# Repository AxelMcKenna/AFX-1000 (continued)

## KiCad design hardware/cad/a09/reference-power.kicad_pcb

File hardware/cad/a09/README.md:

# A09 housing with the actual standalone power PCB

Open `assembly.scad` in OpenSCAD. A09 retains A08's RMX-style panel, 29 guided buttons, ten shaft-mount knobs, selectors, optics and release lever. It integrates the actual 84 × 38 × 1.6 mm in-progress higher-headroom supply PCB instead of the old 78 mm generic reserve. This variant remains separate from the B1 budget design.

The supply board moves from X=207 to X=201 mm, at Y=105 and Z=6.5 mm. Its four mount centres are (205,109), (275,109), (205,139) and (275,139). The right edge remains X=285. At the original position, the allocated test-header top was only 0.09 mm below the Scene Resonance pot body. The new position clears that control without reducing its component reserve. The four power mounts now have Ø2.2 through bores for M2 fixings; actual fastener length, bottom retention and feet remain to be selected.

`integration.py` reads both-side courtyards, through-hole lead positions, four mounting holes and the board outline directly from the current KiCad PCB. All 157 components appear individually. The old generic power-component block is removed. Header/harness, trimmed lead/solder, fixing-head and underside thermal-air allowances are explicit. All body heights are **maximum assembly allocations requiring part selection or measurement**, not catalogue guarantees. The smallest allocated floor clearance is 0.35 mm beneath a bottom 1210 capacitor.

Native checks retain the full button stroke and 0–35° lever sweep. Additional checks expand all power component/lead/head reserves by 0.25 mm against the housing, controls, other boards and electronics reserves, and check one millimetre of unobstructed air under the existing thermal-copper regions. These establish geometric clearance for these allocations only; they do not establish cooling, electrical readiness or physical fit.

A09 is isolated under `build/workspaces/high-headroom-standalone`; the active main working tree's A08 files are untouched. `source.json` records the inherited A08 source hashes. `reference-components.scad` freezes the other A08 electronics reserves. Future PCB placement or height changes require regeneration and renewed native checks.

## Rebuild

From the repository root, use the [uv environment](../../../README.md#python-tooling) and a native OpenSCAD build with Manifold and CGAL:

```sh
uv run --locked python hardware/cad/a09/build.py --openscad /path/to/openscad
uv run --locked python -m unittest discover -s tests -p a09_integration_tests.py -v
uv run --locked python -m hardware.cad.a09.verify
```

Outputs go to `build/artifacts/cad/a09/`. The 3MF is a quantity-correct inventory, not a printer profile. Use `parts.csv` and [PRINTING.md](PRINTING.md) for the prototype mechanical inventory. No print-pack path from A07 or A08 is overwritten. The supplied PCB is an in-progress placement/routing source, not a fabrication file.

Additional standalone circuit boards still need routing and housing integration; the frozen A08 reserves do not represent all higher-headroom circuits. Physical printing, selected-part dimensions, wiring and cable bends, board fastening/feet, control feel, optics, thermal/EMI tests and completion of the electrical system remain open. No complete-unit build readiness is claimed.

A09 now retains its checked 84 × 38 mm supply snapshot in `reference-power.kicad_pcb` and `reference-power-components.json`. The active larger-board integration is [A10](../a10/README.md); rebuilding A09 uses these frozen inputs. The original review archives are unchanged.

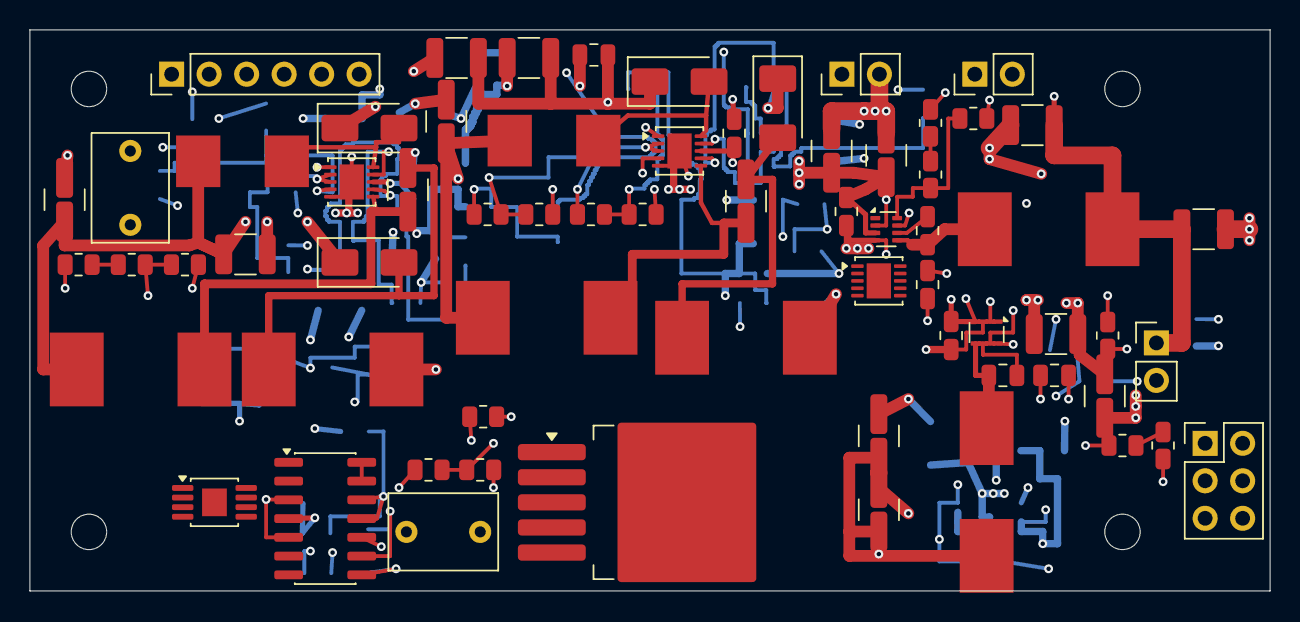
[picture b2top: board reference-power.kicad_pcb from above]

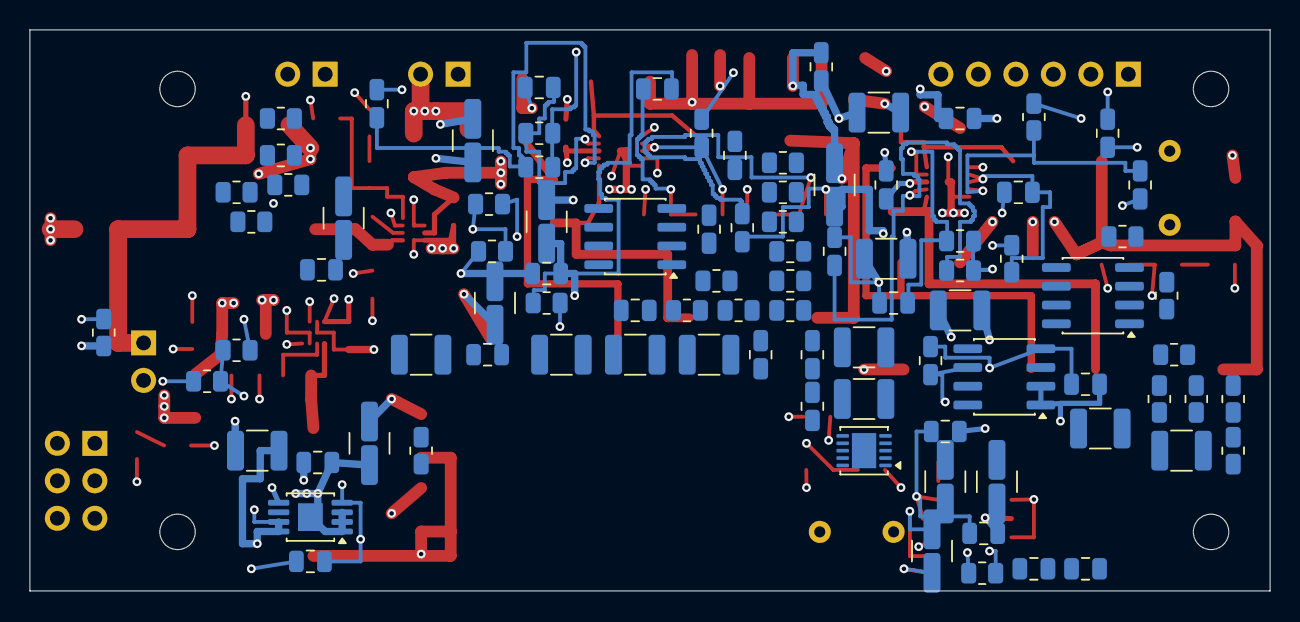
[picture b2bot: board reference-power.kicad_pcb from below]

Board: 6 copper layers, 84.0 x 38.0 mm, 161 parts (91 on the bottom side), 67 nets.

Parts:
C1, C63: 10uF 63V X7R; C_1210_3225Metric
C2, C3, C5, C6, C8, C9, C37, C42, C47, C52, C57, C64, C65, C67, C68, C70: 22uF 50V X7R; C_1210_3225Metric
C4, C7, C10, C22, C29, C35, C38, C40, C43, C45, C48, C50, C53, C55, C58, C59, C61, C66, C69, C71: 100nF 50V X7R; C_0805_2012Metric
C11, C16, C23, C30, C72: 100nF 16V X7R; C_0805_2012Metric
C12, C14, C73, C75: 68pF 50V C0G 5%; C_0805_2012Metric
C13, C15, C74, C76: 330nF 16V X7R; C_0805_2012Metric
C17: 1uF 16V X7R; C_0805_2012Metric
C18, C19, C25, C26: 22uF 16V X7R; C_1210_3225Metric
C20, C21, C27, C28: 10uF 25V X7R; C_1210_3225Metric
C24: 33nF 16V X7R; C_0805_2012Metric
C31: 2.2uF 16V X7R; C_0805_2012Metric
C32, C33: 1uF film 63V 10% MKS2C041001F00KSSD; C_Rect_L7.2mm_W5.0mm_P5.00mm
C34, C39, C44, C49, C54: 47nF 50V C0G 5%; C_1210_3225Metric
C36, C41, C46, C51, C56: 10uF 50V X7R; C_1210_3225Metric
C60, C62: 1uF 50V X7R; C_0805_2012Metric
D1, D2, D3, D4: SS16-E3/61T; D_SMA
H1, H2, H3, H4: M2_CLEARANCE; M2_Clearance
J1, J3, J5: Header2; PinHeader_1x02_P2.54mm_Vertical
J2: Header6; PinHeader_1x06_P2.54mm_Vertical
J4: Header6; PinHeader_2x03_P2.54mm_Vertical
L1, L6: 33uH 20% SRP7050WA-330M; SRP7050WA
L2, L3, L7, L8: 68uH 20% SRP1050WA-680M; SRP1050WA
L4, L5: 10uH 20% SRP1050WA-100M; SRP1050WA
R1: 300k 0.01% 5ppm; R_0805_2012Metric
R2, R3, R4, R45, R46: 15k 0.01% 5ppm; R_0805_2012Metric
R5, R20, R21, R34, R35: 330k 0.01% 5ppm; R_0805_2012Metric
R6, R7, R49, R50: 4.7k 1%; R_0805_2012Metric
R8, R12: 10k 1%; R_0805_2012Metric
R9, R13: 22k 1%; R_0805_2012Metric
R10: 10.5k 0.01% 5ppm; R_0805_2012Metric
R11, R16: 2k 0.01% 5ppm; R_0805_2012Metric
R14: 12.4k 0.01% 5ppm; R_0805_2012Metric
R15: 100 0.01% 5ppm; R_0805_2012Metric
R17, R19: 1k 1%; R_0805_2012Metric
R18: 100k 1%; R_0805_2012Metric
R22, R27, R30, R31, R36, R41: 100k 0.01% 5ppm; R_0805_2012Metric
R23, R28, R32, R37, R42: 6.8k 1%; R_0805_2012Metric
R24, R38: 9.09k 1%; R_0805_2012Metric
R25, R39, R47: 200k 0.01% 5ppm; R_0805_2012Metric
R26, R40: 180k 0.01% 5ppm; R_0805_2012Metric
R29, R43: 5.62k 1%; R_0805_2012Metric
R33: 2.21k 1%; R_0805_2012Metric
R44: 240k 0.01% 5ppm; R_0805_2012Metric
R48: 54.9k 0.01% 5ppm; R_0805_2012Metric
R51: 10 0.01% 5ppm; R_0805_2012Metric
U1, U13: LT3471EDD#PBF; DFN-10-1EP_3x3mm_P0.5mm_EP1.65x2.38mm
U2, U3: TPS62933FDRLR; SOT-583-8
U4: REF5025EIDR; SOIC-8_3.9x4.9mm_P1.27mm
U5: OPA4192ID; SOIC-14_3.9x8.7mm_P1.27mm
U6: OPA2192ID; SOIC-8_3.9x4.9mm_P1.27mm
U7, U9: LT3080IMS8E#PBF; MSOP-8-1EP_3x3mm_P0.65mm_EP1.68x1.88mm
U8: LT3080IQ#PBF; TO-263-5_TabPin3
U10, U11: LT3090IDD#PBF; DFN-10-1EP_3x3mm_P0.5mm_EP1.65x2.38mm
U12: LT1634AIS8-2.5#PBF; SOIC-8_3.9x4.9mm_P1.27mm

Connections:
/5V_DIG_SRC: C18.1, C19.1, C30.1, J3.1, L4.2, R6.1, R7.1, R10.1, R49.1, R50.1, U4.1, U4.2, U10.5, U11.5
/AGND: C2.2, C3.2, C4.2, C5.2, C6.2, C7.2, C8.2, C9.2, C10.2, C11.2, C13.2, C15.2, C17.2, C18.2, C19.2, C20.2, C21.2, C22.2, C24.2, C25.2, C26.2, C27.2, C28.2, C29.2, C30.2, C31.2, C32.2, C33.2, C35.2, C36.2, C37.2, C38.2, C40.2, C41.2, C42.2, C43.2, C45.2, C46.2, C47.2, C48.2, C50.2, C51.2, C52.2, C53.2, C55.2, C56.2, C57.2, C58.2, C59.2, C60.2, C61.2, C62.2, C64.2, C65.2, C66.2, C67.2, C68.2, C69.2, C70.2, C71.2, C72.2, C74.2, C76.2, D2.1, D4.1, J1.2, J2.2, J3.2, J4.2, J5.1, R3.2, R9.2, R11.2, R13.2, R16.2, R22.2, R24.2, R27.2, R29.2, R31.2, R33.2, R36.2, R38.2, R41.2, R43.2, R45.2, U1.5, U1.11, U2.4, U3.4, U4.4, U5.11, U5.12, U6.8, U10.3, U11.3, U12.6, U13.5, U13.11
/CUK_NODE: C1.2, D2.2, L3.1
/DIG_BST: C16.1, U2.6
/DIG_FB: R11.1, R51.2, U2.8
/DIG_FB_TRIM: R10.2, R51.1
/DIG_SS: C17.1, U2.7
/DIG_SW: C16.2, L4.1, U2.5
/LO_CUK_NODE: C63.2, D4.2, L8.1
/LO_N_FB: C75.2, R46.2, R47.1, U13.4
/LO_N_RMID: R47.2, R48.1
/LO_N_SS: C76.1, R50.2, U13.7
/LO_N_SW: C63.1, L7.2, U13.6
/LO_P_FB: C73.2, R44.2, R45.1, U13.1
/LO_P_SS: C74.1, R49.2, U13.9
/LO_P_SW: D3.2, L6.2, U13.10
/LO_REF_1V: C72.1, R46.1, U13.2, U13.3
/N12_DRIVE: C54.1, R42.1, U6.7
/N12_FB: C54.2, R40.2, R41.1, U6.6
/N12_RMID: R39.2, R40.1
/N12_SET: C55.1, R39.1, R42.2, U11.4
/N12_SRC: C57.1, C58.1, J2.5, R43.1, U11.1, U11.2
/N19_DRIVE: C49.1, R37.1, U6.1
/N19_FB: C49.2, R35.2, R36.1, U6.2
/N19_RMID: R34.2, R35.1
/N19_SET: C50.1, R34.1, R37.2, U10.4
/N19_SRC: C52.1, C53.1, J2.3, R38.1, U10.1, U10.2
/NREF_2V5: R18.1, R19.1, U12.4, U12.5
/NREF_FILTER: C33.1, R19.2, U6.3, U6.5
/P12_DRIVE: C39.1, R28.1, U5.7
/P12_FB: C39.2, R26.2, R27.1, U5.6
/P12_RMID: R25.2, R26.1
/P12_SET: C40.1, R25.1, R28.2, U8.2
/P12_SRC: C42.1, C43.1, J2.4, R29.1, U8.3
/P19_DRIVE: C34.1, R23.1, U5.1
/P19_FB: C34.2, R21.2, R22.1, U5.2
/P19_RMID: R20.2, R21.1
/P19_SET: C35.1, R20.1, R23.2, U7.4
/P19_SRC: C37.1, C38.1, J2.1, R24.1, U7.1, U7.2, U7.3, U7.9
/POWER_READY: J5.2, R8.1, R12.1
/PREF_2V5: C31.1, R17.1, U4.6
/PREF_FILTER: C32.1, R17.2, U5.3, U5.5, U5.10
/PRE_BST: C23.1, U3.6
/PRE_FB: R15.2, R16.1, U3.8
/PRE_RMID: R14.2, R15.1
/PRE_SS: C24.1, U3.7
/PRE_SW: C23.2, L5.1, U3.5
/RAW_N17: C56.1, C67.1, C68.1, C69.1, C75.1, J4.5, L8.2, R48.2, U11.8, U11.9, U11.10, U11.11
/RAW_N22: C8.1, C9.1, C10.1, C14.1, C51.1, C61.1, C62.1, J4.3, L3.2, R5.2, R18.2, U6.4, U10.8, U10.9, U10.10, U10.11
/RAW_N_FB: C14.2, R4.2, R5.1, U1.4
/RAW_N_SS: C15.1, R7.2, U1.7
/RAW_N_SW: C1.1, L2.2, U1.6
/RAW_P17: C41.1, C64.1, C65.1, C66.1, C73.1, D3.1, J4.4, R44.1, U8.4, U8.5
/RAW_P22: C5.1, C6.1, C7.1, C12.1, C36.1, C59.1, C60.1, D1.1, J4.1, R1.1, U5.4, U7.5, U7.7, U7.8
/RAW_P_FB: C12.2, R2.2, R3.1, U1.1
/RAW_P_RMID: R1.2, R2.1
/RAW_P_SS: C13.1, R6.2, U1.9
/RAW_P_SW: D1.2, L1.2, U1.10
/SPARE_OUT: U5.13, U5.14
/SUPPLY_ENABLE: R8.2, R9.1, R12.2, R13.1, U2.2, U3.2
/SW_REF_1V: C11.1, R4.1, U1.2, U1.3
/V5_PRE: C25.1, C26.1, C46.1, J4.6, L5.2, R14.1, U9.7, U9.8
/V5_REG_DRIVE: C44.1, R32.1, U5.8
/V5_REG_FB: C44.2, R30.2, R31.1, U5.9
/V5_REG_SET: C45.1, R30.1, R32.2, U9.4
/V5_REG_SRC: C47.1, C48.1, J2.6, R33.1, U9.1, U9.2, U9.3, U9.9
/VIN_PROTECTED: C2.1, C3.1, C4.1, C20.1, C21.1, C22.1, C27.1, C28.1, C29.1, C70.1, C71.1, J1.1, L1.1, L2.1, L6.1, L7.1, U1.8, U2.3, U3.3, U9.5, U13.8

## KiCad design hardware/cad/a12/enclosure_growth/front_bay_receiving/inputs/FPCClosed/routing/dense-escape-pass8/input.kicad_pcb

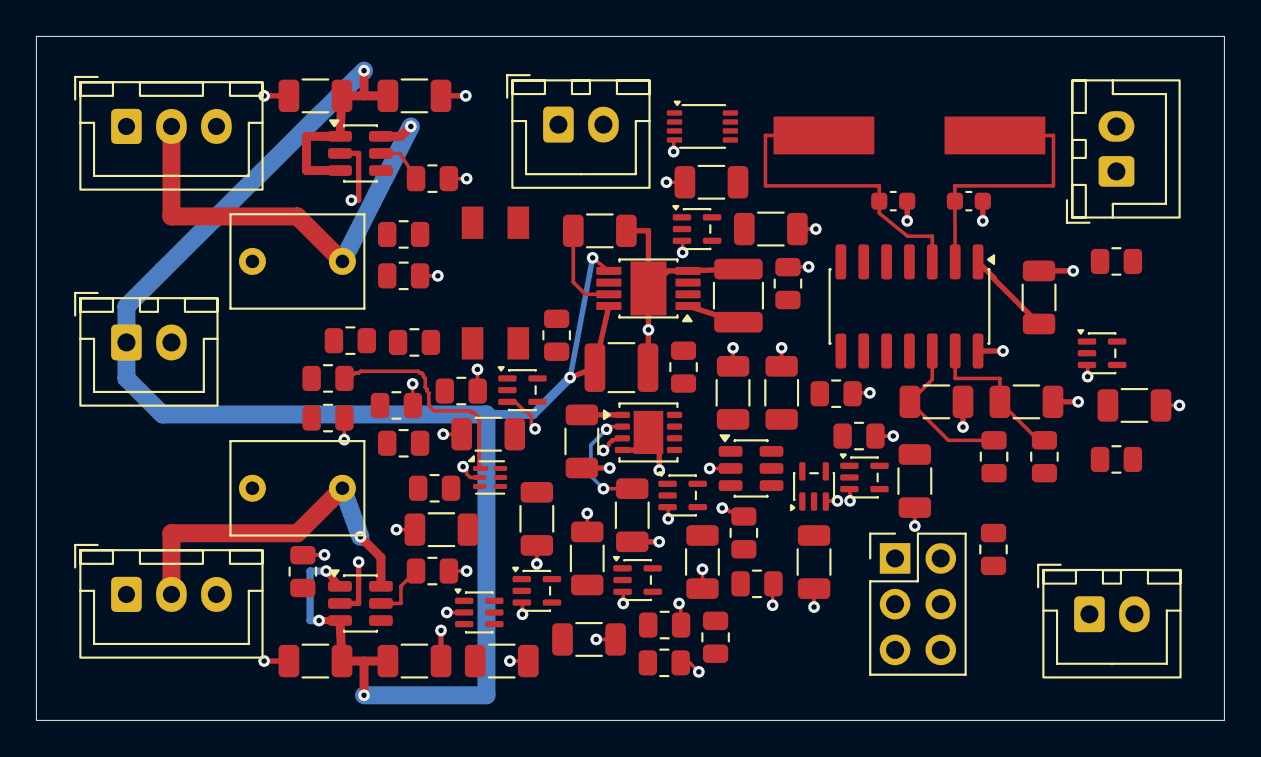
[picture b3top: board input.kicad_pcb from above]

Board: 4 copper layers, 66.0 x 38.0 mm, 84 parts (0 on the bottom side), 45 nets.

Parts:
C1, C2: 10uF 25V C3225X7R1E106K250AC; Capacitor_SMD__C_1210_3225Metric
C3, C14, C22, C23: 10nF 50V C0G C1206C103J5GACTU; Capacitor_SMD__C_1206_3216Metric
C4, C5, C6, C8, C9, C10, C11, C12, C13, C15, C16, C17, C18, C19, C24: 100nF 25V C0G C1206C104J3GACTU; Capacitor_SMD__C_1206_3216Metric
C7: 2.7nF 50V C0G C1206C272J5GACTU; Capacitor_SMD__C_1206_3216Metric
C20, C21: 15pF 50V C0G5% C0603C150J5GACTU; Capacitor_SMD__C_0603_1608Metric
C201, C202, C301, C302: 100nF25V C0G5% C1206C104J3GACTU; Capacitor_SMD__C_1206_3216Metric
C203, C303: 1uF63V10% WIMA MKS2C041001F00KSSD; Capacitor_THT__C_Rect_L7.2mm_W5.0mm_P5.00mm
J2, J3, J4, J201: JST B2B-XH-A / XHP-2 / SXH-001T-P0.6; Connector_JST__JST_XH_B2B-XH-A_1x02_P2.50mm_Vertical
J5: AVRISP2x3 target-powered3.3V sense ONLY; Connector_PinHeader_2.54mm__PinHeader_2x03_P2.54mm_Vertical
J202, J203: JST B3B-XH-A / XHP-3 / SXH-001T-P0.6; Connector_JST__JST_XH_B3B-XH-A_1x03_P2.50mm_Vertical
R1, R16, R17, R21, R23: 1k 0.1%25ppm TNPW08051K00BEEA; Resistor_SMD__R_0805_2012Metric
R2, R6, R10, R13, R202, R302: 10k 0.1%25ppm TNPW080510K0BEEA; Resistor_SMD__R_0805_2012Metric
R3, R4, R5, R7, R14, R15: 47k 0.1%25ppm TNPW080547K0BEEA; Resistor_SMD__R_0805_2012Metric
R8: 68k 0.1%25ppm TNPW080568K0BEEA; Resistor_SMD__R_0805_2012Metric
R9: 39k 0.1%25ppm TNPW080539K0BEEA; Resistor_SMD__R_0805_2012Metric
R11: 56.2k 0.1%25ppm TNPW080556K2BEEA; Resistor_SMD__R_0805_2012Metric
R12, R24, R201, R203, R301, R303: 100k 0.1%25ppm TNPW0805100KBEEA; Resistor_SMD__R_0805_2012Metric
R20, R22: 20k 0.1%25ppm TNPW080520K0BEEA; Resistor_SMD__R_0805_2012Metric
U1: ATtiny84A-SSUR; Package_SO__SOIC-14_3.9x8.7mm_P1.27mm
U2: TPS7A1633DGNR; TI_DGN0008C
U3: SN74LVC2G17DCKR; Package_TO_SOT_SMD__SOT-363_SC-70-6
U4: TPS3431SDRBR; Package_SON__VSON-8-1EP_3x3mm_P0.65mm_EP1.65x2.4mm
U5: SN74AUP1G17DCKR; Package_TO_SOT_SMD__SOT-353_SC-70-5
U6: SN74LVC1T45DBVR; Package_TO_SOT_SMD__SOT-23-6
U7: SN74LVC1G14DCKR; Package_TO_SOT_SMD__SOT-353_SC-70-5
U8: SN74LVC1G74DCUR; TI_DCU0008A
U9: TPS389001DSET; Package_SON__WSON-6_1.5x1.5mm_P0.5mm
U10, U11: SN74LVC1G17DCKR; Package_TO_SOT_SMD__SOT-353_SC-70-5
U12, U13: SN74LVC1G08DCKR; Package_TO_SOT_SMD__SOT-353_SC-70-5
U14: SN74LVC1G06DCKR; Package_TO_SOT_SMD__SOT-353_SC-70-5
U15: TLP175A(TPL,E); RMX_FH02__TLP175A_11-4M1S_Receiving
U16: SN74LVC1G34DCKR; Package_TO_SOT_SMD__SOT-353_SC-70-5
U201, U301: TPS2553DBVR-1; Package_TO_SOT_SMD__SOT-23-6
X1: ABLS-4.000MHZ-12-D4Y-T; RMX_FH02__ABLS_Manufacturer_Land

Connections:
/E28_POWER_RUN: J4.2, U15.6
/FAN5V_IN: C1.1, C10.1, C11.1, C12.1, C13.1, C15.1, C201.1, C202.1, C301.1, C302.1, J201.1, R1.1, R10.1, R11.1, U2.5, U2.8, U6.6, U7.5, U8.2, U8.7, U8.8, U9.3, U9.4, U10.5, U201.1, U201.3, U301.1, U301.3
/FAN_L_5V: C203.1, J202.2, R202.1, R203.1, U201.6
/FAN_L_ILIM: R201.1, U201.5
/FAN_L_TACH: J202.3, R14.1, R202.2, U3.1
/FAN_R_5V: C303.1, J203.2, R302.1, R303.1, U301.6
/FAN_R_ILIM: R301.1, U301.5
/FAN_R_TACH: J203.3, R15.1, R302.2, U3.3
/FAULT_CLK: U7.4, U8.1
/GND: C1.2, C2.2, C3.2, C4.2, C5.2, C6.2, C7.2, C8.2, C9.2, C10.2, C11.2, C12.2, C13.2, C14.2, C15.2, C16.2, C17.2, C18.2, C19.2, C20.2, C21.2, C22.2, C23.2, C24.2, C201.2, C202.2, C203.2, C301.2, C302.2, C303.2, J2.2, J3.2, J5.6, J201.2, J202.1, J203.1, R3.2, R4.2, R8.2, R9.2, R12.2, R13.2, R14.2, R15.2, R24.2, R201.2, R203.2, R301.2, R303.2, U1.14, U2.4, U2.9, U3.2, U4.4, U4.9, U5.3, U6.2, U7.3, U8.4, U9.2, U10.3, U11.3, U12.3, U13.3, U14.3, U16.3, U201.2, U301.2
/HEALTH_AND_WD: U12.4, U13.1
/HEARTBEAT: R4.1, U1.11, U16.2
/HEARTBEAT_FAST: U4.6, U16.4
/HW_NOFAULT: U11.4, U13.2
/HW_NOFAULT_5: R9.1, U8.3, U11.2
/ISP_MISO: J5.1, U1.8
/ISP_MOSI: J5.4, U1.7
/ISP_SCK: J5.3, U1.9
/LDO_DELAY: C3.1, U2.7
/LEAF_PERMISSION: R13.1, U13.4, U14.2
/LED_A: R1.2, R2.1, U15.1
/LED_K: R2.2, U14.4, U15.3
/MCU_HEALTH: R3.1, U1.6, U12.1
/MCU_RESET_N: J5.5, R6.2, U1.4
/MCU_TACH_L: R16.2, U1.10
/MCU_TACH_R: R17.2, U1.5
/P03_POWER_RUN: J4.1, U15.4
/RAW_CLEAR_FAST: U8.6, U10.4
/RAW_CLEAR_N: R10.2, U9.6, U10.2
/RAW_POR_CT: C14.1, U9.5
/RAW_POR_SENSE: R11.2, R12.1, U9.1
/TACH_L_BUF: R16.1, U3.6
/TACH_R_BUF: R17.1, U3.4
/TEMP_L_ADC: C22.1, R21.2, U1.13
/TEMP_L_NODE: J2.1, R20.2, R21.1
/TEMP_R_ADC: C23.1, R23.2, U1.12
/TEMP_R_NODE: J3.1, R22.2, R23.1
/V3V3: C2.1, C4.1, C5.1, C6.1, C8.1, C9.1, C16.1, C17.1, C18.1, C19.1, C24.1, J5.2, R5.1, R6.1, R7.1, R20.1, R22.1, R24.1, U1.1, U2.1, U3.5, U4.1, U4.5, U5.5, U6.1, U6.5, U11.5, U12.5, U13.5, U14.5, U16.5
/WD_CWD: C7.1, U4.2
/WD_EN: R7.2, U4.3
/WD_OK: R5.2, U2.3, U4.7, U4.8, U5.2
/WD_OK_5: R8.1, U6.4, U7.2
/WD_OK_FAST: U5.4, U6.3, U12.2
/XTAL1: C20.1, U1.2, X1.1
/XTAL2: C21.1, U1.3, X1.2
